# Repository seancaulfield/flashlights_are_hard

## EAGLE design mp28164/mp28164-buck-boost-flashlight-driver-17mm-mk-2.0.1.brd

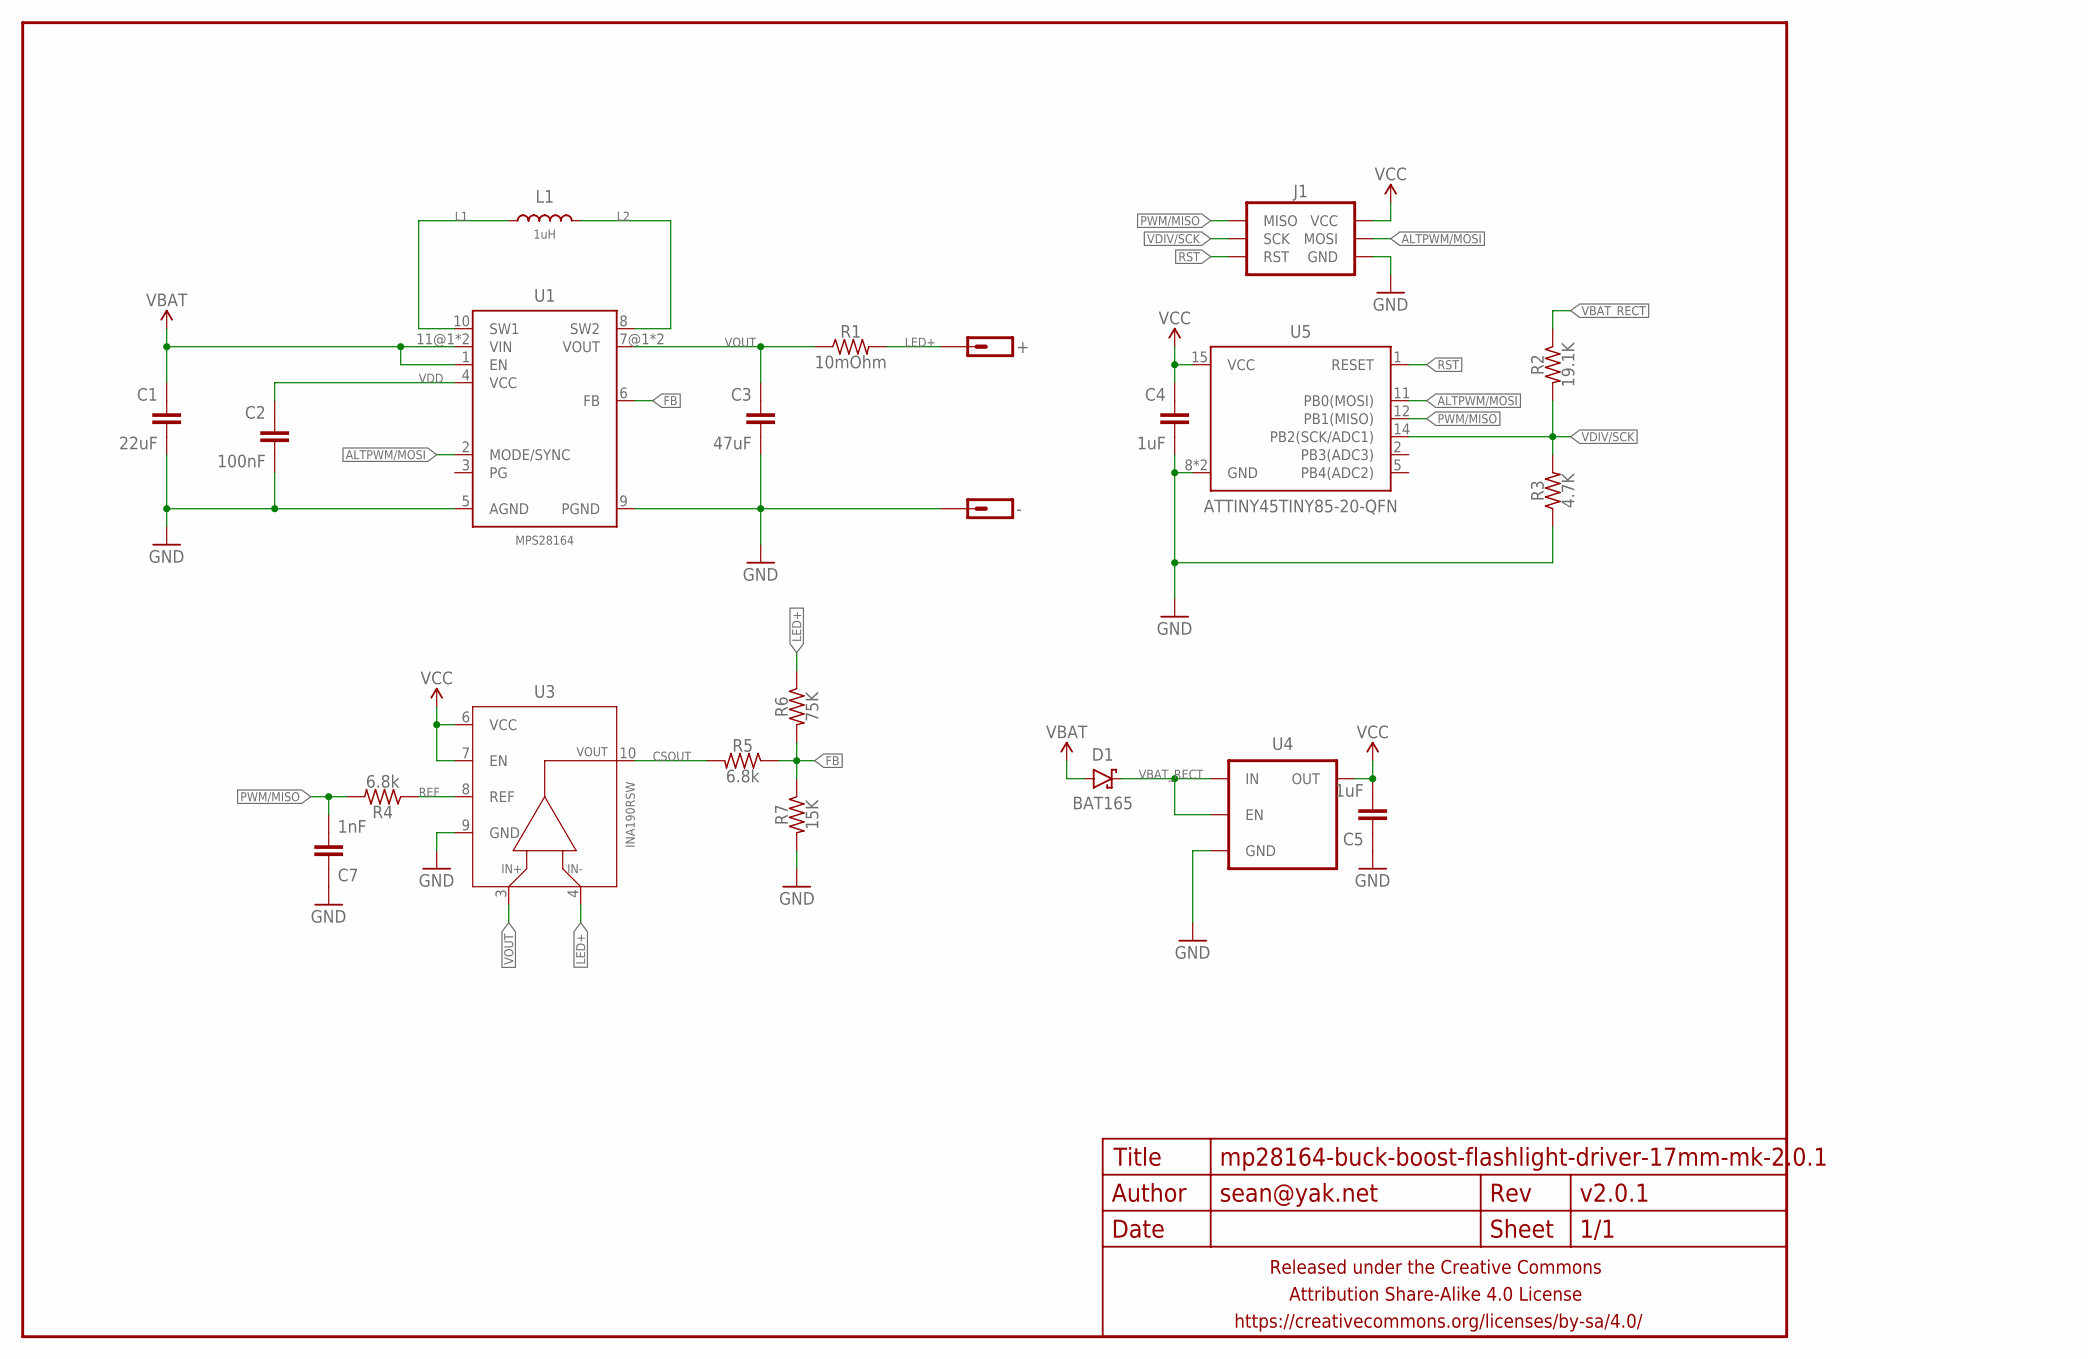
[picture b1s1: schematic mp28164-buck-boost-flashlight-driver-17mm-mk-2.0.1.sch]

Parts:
+: M01SMD-1.6MMX3.2MM-NS; 1X01-SMD-1.6MMX3.2MM-NS
-: M01SMD-1.6MMX3.2MM-NS; 1X01-SMD-1.6MMX3.2MM-NS
C1: 22uF; C1206
C2: 100nF; C0402
C3: 47uF; C1206
C4, C5: 1uF; C0402
C7: 1nF; C0402
D1: BAT165; SOD323-SCHOTTKY
FRAME1: FRAME-LETTERNO_PACKAGE; DUMMY
J1: AVR_SPI_PRG_6SMD-1.27MM; 2X3-1.27MM-SMD
L1: 1uH; XAL7070
R1: 10mOhm; R1206
R2: 19.1K; R0402
R3: 4.7K; R0402
R4, R5: 6.8k; R0402
R6: 75K; R0402
R7: 15K; R0402
U1: MPS28164
U3: INA190RSW; UQFN-10
U4: V_REG_ENTLV700; SC70
U5: ATTINY45TINY85-20-QFN; QFN20

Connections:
ALTPWM/MOSI: J1.4 (MOSI), U1.2 (MODE/SYNC), U5.11 (PB0(MOSI))
CSOUT: R5.2, U3.10 (OUT)
FB: R5.1, R6.2, R7.1, U1.6 (FB)
GND: -.P$1, C1.2, C2.2, C3.2, C4.2, C5.1, C7.1, J1.6 (GND), R3.1, R7.2, U1.5 (AGND), U1.9 (PGND), U3.9 (GND), U4.2 (GND), U5.8 (GND), U5.PAD (GND)
L1: L1.P$1 (1), U1.10 (SW1)
L2: L1.P$2 (2), U1.8 (SW2)
LED+: +.P$1, R1.2, R6.1, U3.4 (VIN-)
PWM/MISO: C7.2, J1.1 (MISO), R4.2, U5.12 (PB1(MISO))
REF: R4.1, U3.8 (REF)
RST: J1.5 (RST), U5.1 (RESET)
VBAT: C1.1, D1.A, U1.1 (EN), U1.11@1 (VIN), U1.11@2 (VIN)
VBAT_RECT: D1.C, R2.1, U4.1 (IN), U4.3 (EN)
VCC: C4.1, C5.2, J1.2 (VCC), U3.6 (VCC), U3.7 (EN), U4.5 (OUT), U5.15 (VCC)
VDD: C2.1, U1.4 (VCC)
VDIV/SCK: J1.3 (SCK), R2.2, R3.2, U5.14 (PB2(SCK/ADC1))
VOUT: C3.1, R1.1, U1.7@1 (VOUT), U1.7@2 (VOUT), U3.3 (VIN+)

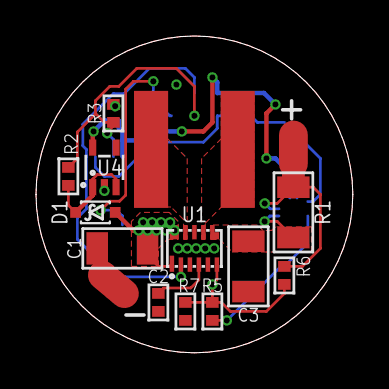
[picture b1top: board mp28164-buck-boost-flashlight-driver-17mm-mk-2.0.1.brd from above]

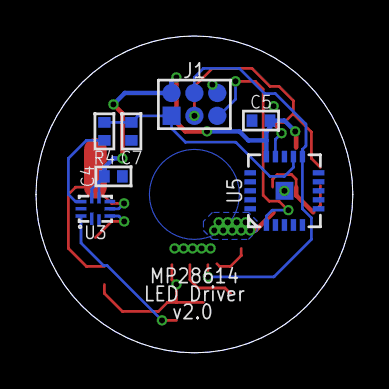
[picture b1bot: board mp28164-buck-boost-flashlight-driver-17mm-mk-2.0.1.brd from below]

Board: 2 copper layers, 17.6 x 17.6 mm, 23 parts (7 on the bottom side), 16 nets.

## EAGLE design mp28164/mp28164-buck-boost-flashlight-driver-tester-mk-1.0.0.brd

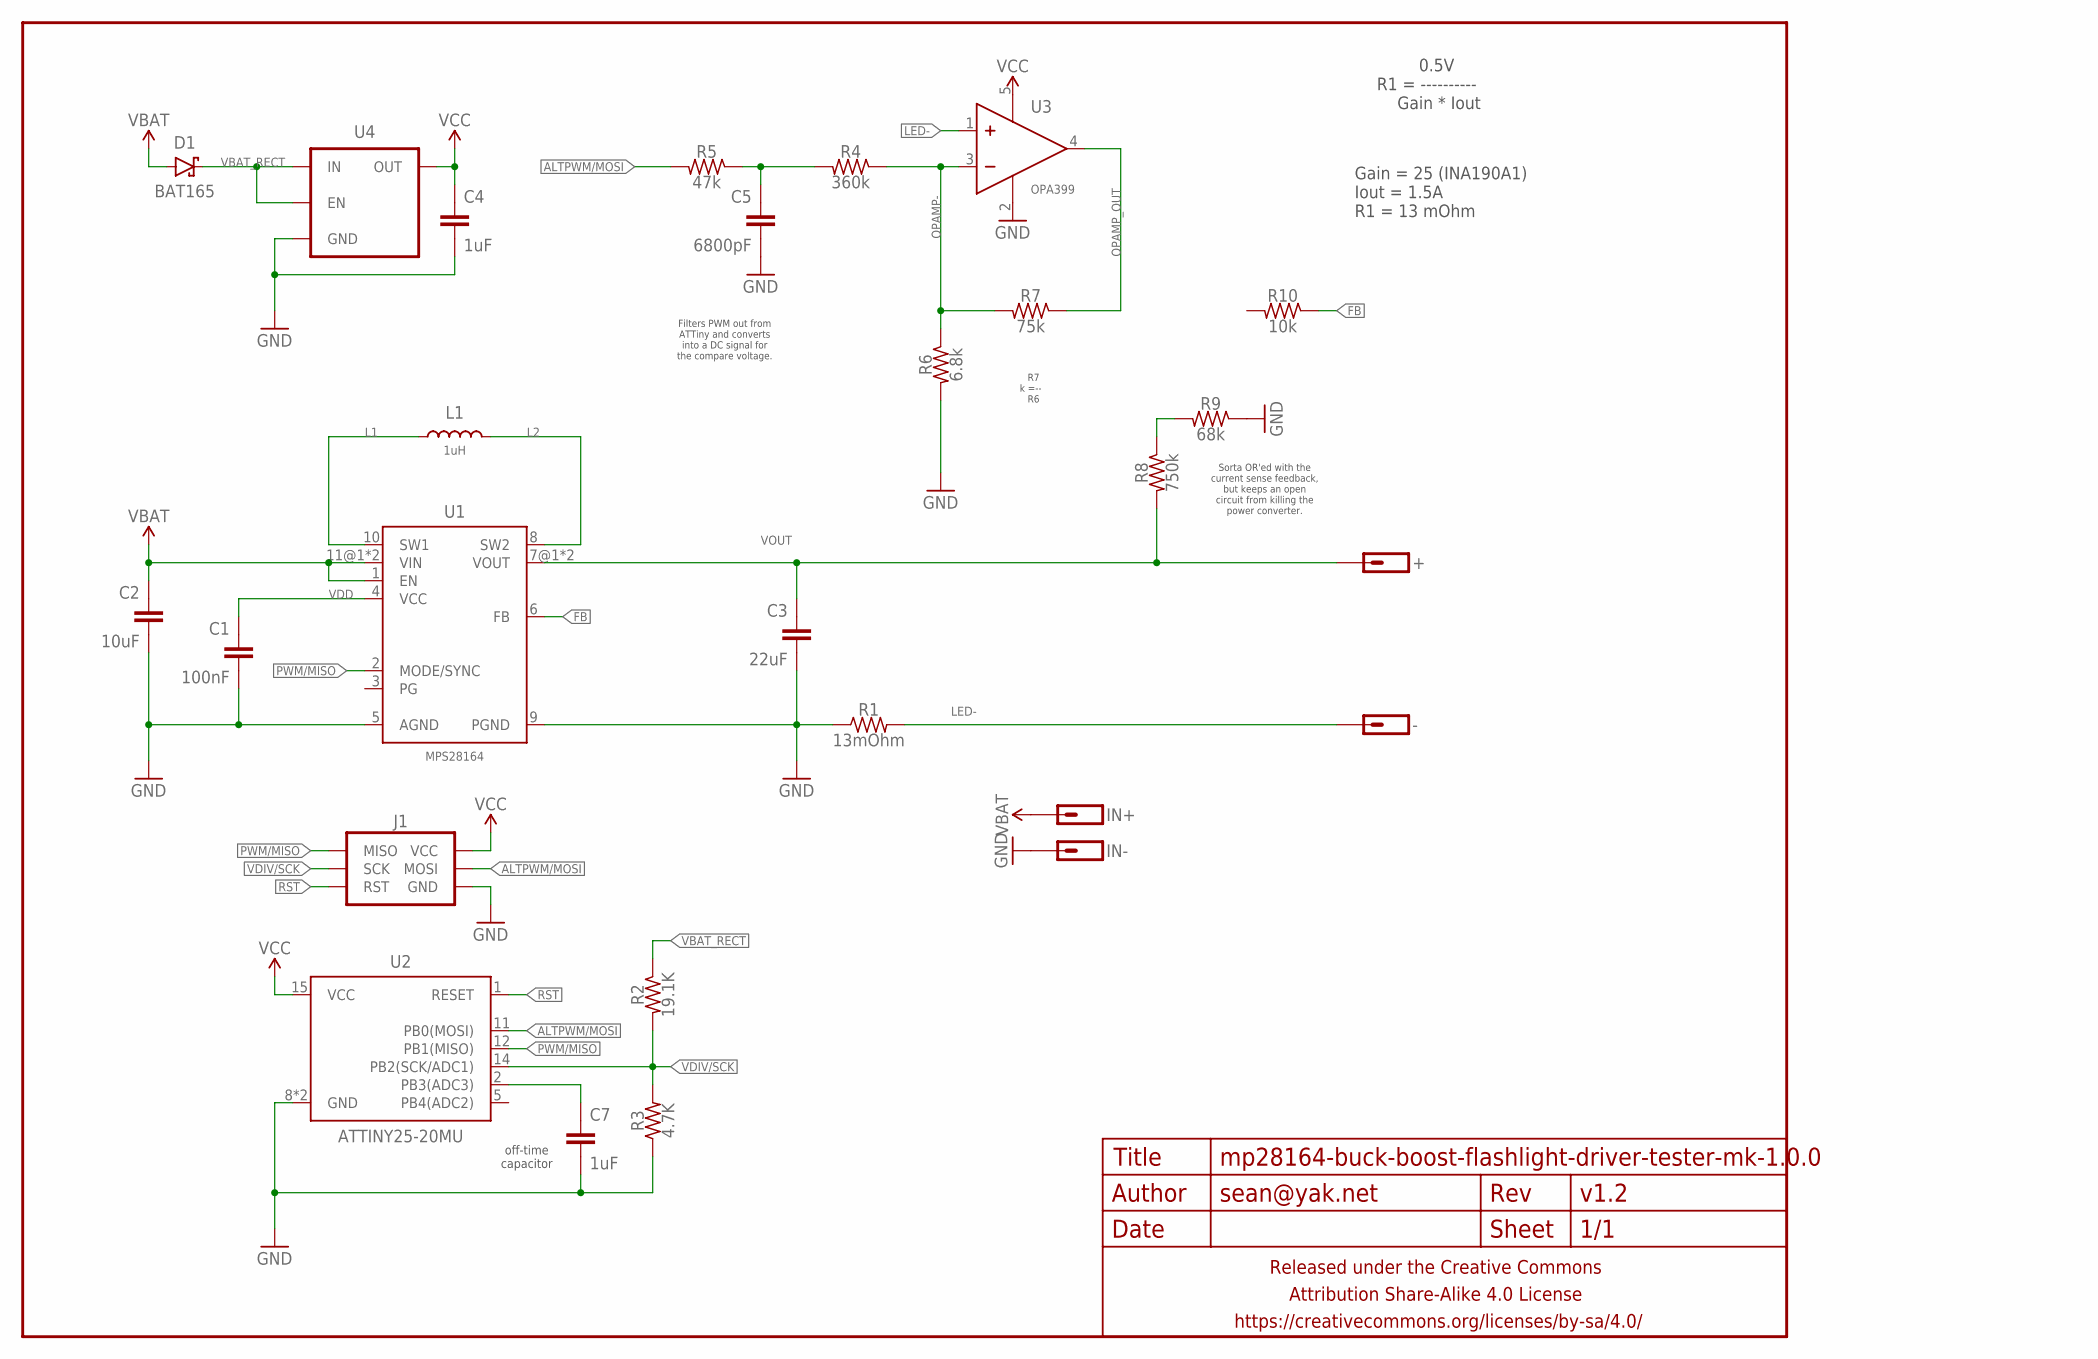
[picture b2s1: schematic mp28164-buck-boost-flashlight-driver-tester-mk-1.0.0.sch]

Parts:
+: M01PTH-1MM-CIR-NS; 1X01-1MM-CIR-NS
-: M01PTH-1MM-CIR-NS; 1X01-1MM-CIR-NS
C1: 100nF; C0402
C2: 10uF; C0805-TIGHTER
C3: 22uF; C0805-TIGHTER
C4, C7: 1uF; C0402
C5: 6800pF; C0402
D1: BAT165; SOD323-SCHOTTKY
FRAME1: FRAME-LETTERNO_PACKAGE; DUMMY
IN+: M01PTH-1MM-CIR-NS; 1X01-1MM-CIR-NS
IN-: M01PTH-1MM-CIR-NS; 1X01-1MM-CIR-NS
J1: AVR_SPI_PRG_6SMD-1.27MM; 2X3-1.27MM-SMD
L1: 1uH; XAR7030
R1: 13mOhm; R0805-TIGHTER
R2: 19.1K; R0402
R3: 4.7K; R0402
R4: 360k; R0402
R5: 47k; R0402
R6: 6.8k; R0402
R7: 75k; R0402
R8: 750k; R0402
R9: 68k; R0402
R10: 10k; R0402
U1: MPS28164
U2: ATTINY25-20MU; QFN20
U3: OPA399; SC70
U4: V_REG_ENTLV700; SC70

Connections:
ALTPWM/MOSI: J1.4 (MOSI), R5.2, U2.11 (PB0(MOSI))
FB: R10.1, U1.6 (FB)
GND: C1.2, C2.2, C3.2, C4.2, C5.2, C7.2, IN-.1, J1.6 (GND), R1.1, R3.1, R6.2, R9.1, U1.5 (AGND), U1.9 (PGND), U2.8 (GND), U2.PAD (GND), U3.2 (V-), U4.2 (GND)
L1: L1.P$1 (1), U1.10 (SW1)
L2: L1.P$2 (2), U1.8 (SW2)
LED-: -.1, R1.2, U3.1 (IN+)
unnamed: C5.1, R4.2, R5.1
unnamed: R8.1, R9.2
unnamed: C7.1, U2.2 (PB3(ADC3))
OPAMP-: R4.1, R6.1, R7.2, U3.3 (IN-)
OPAMP_OUT: R7.1, U3.4 (OUT)
PWM/MISO: J1.1 (MISO), U1.2 (MODE/SYNC), U2.12 (PB1(MISO))
RST: J1.5 (RST), U2.1 (RESET)
VBAT: C2.1, D1.A, IN+.1, U1.1 (EN), U1.11@1 (VIN), U1.11@2 (VIN)
VBAT_RECT: D1.C, R2.1, U4.1 (IN), U4.3 (EN)
VCC: C4.1, J1.2 (VCC), U2.15 (VCC), U3.5 (V+), U4.5 (OUT)
VDD: C1.1, U1.4 (VCC)
VDIV/SCK: J1.3 (SCK), R2.2, R3.2, U2.14 (PB2(SCK/ADC1))
VOUT: +.1, C3.1, R8.2, U1.7@1 (VOUT), U1.7@2 (VOUT)

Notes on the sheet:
off-time capacitor
0.5V R1 = ---------- Gain * Iout
Gain = 25 (INA190A1) Iout = 1.5A R1 = 13 mOhm
Filters PWM out from ATTiny and converts into a DC signal for the compare voltage.
R7 k =-- R6
Sorta OR'ed with the current sense feedback, but keeps an open circuit from killing the power converter.

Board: 2 copper layers, 28 parts (1 on the bottom side), 19 nets, no tracks yet.

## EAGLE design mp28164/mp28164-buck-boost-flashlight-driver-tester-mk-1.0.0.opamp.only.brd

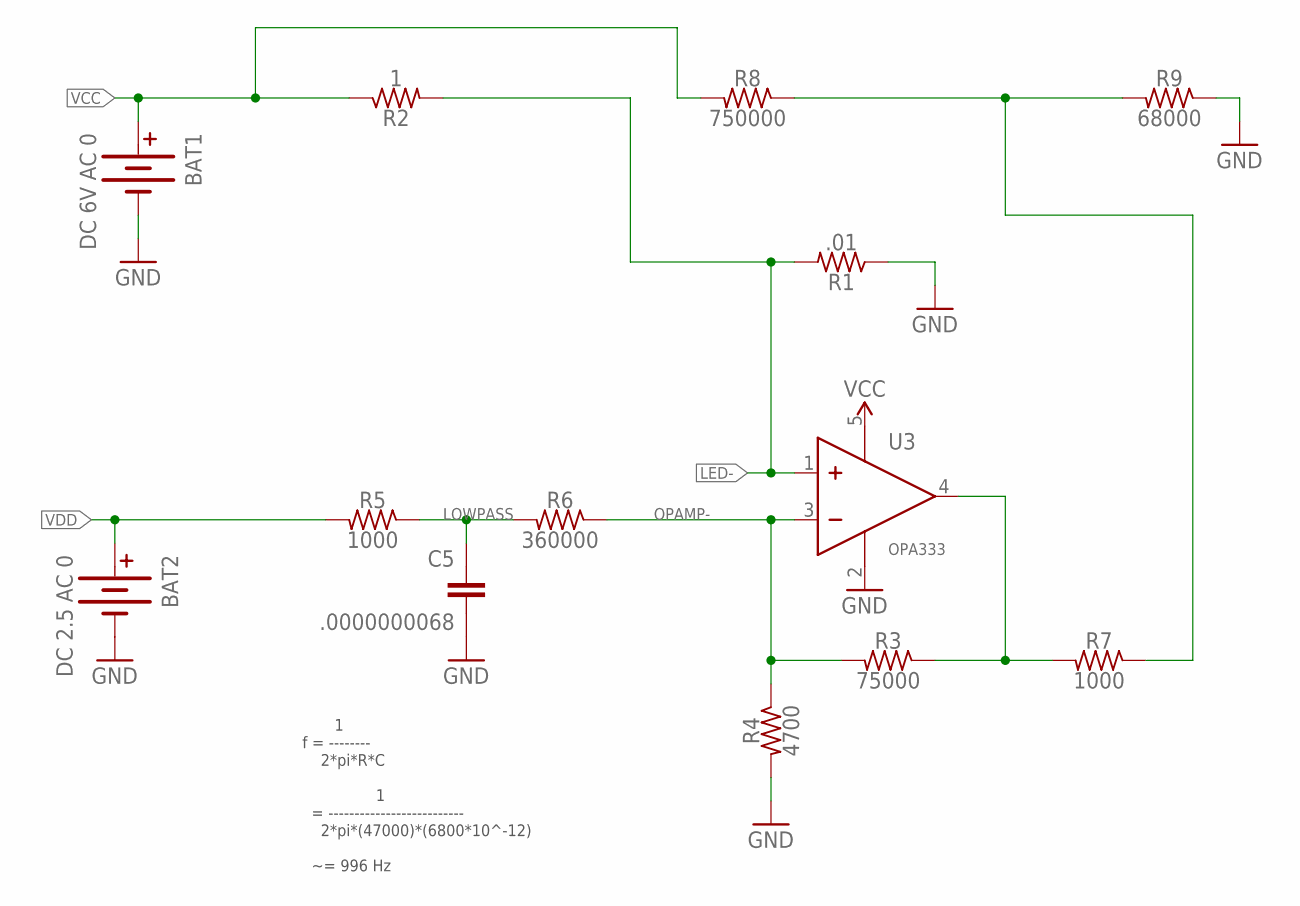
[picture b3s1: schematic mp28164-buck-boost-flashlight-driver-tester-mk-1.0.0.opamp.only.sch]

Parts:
BAT1: DC 6V AC 0; BATTCON_9V
BAT2: DC 2.5 AC 0; BATTCON_9V
C5: .0000000068; C0402
R1: .01; R0805-TIGHTER
R2: 1; R0402
R3: 75000; R0402
R4: 4700; R0402
R5, R7: 1000; R0402
R6: 360000; R0402
R8: 750000; R0402
R9: 68000; R0402
U3: OPA333; SC70

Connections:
GND: BAT1.-, BAT2.-, C5.2, R1.1, R4.2, R9.1, U3.2 (V-)
LED-: R1.2, R2.2, U3.1 (IN+)
LOWPASS: C5.1, R5.1, R6.2
unnamed: R7.1, R8.1, R9.2
OPAMP-: R3.2, R4.1, R6.1, U3.3 (IN-)
OPAMP_OUT: R3.1, R7.2, U3.4 (OUT)
VCC: BAT1.+, R2.1, R8.2, U3.5 (V+)
VDD: BAT2.+, R5.2

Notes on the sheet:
1 f = -------- 2*pi*R*C 1 = -------------------------- 2*pi*(47000)*(6800*10^-12) ~= 996 Hz

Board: 2 copper layers, 13 parts (0 on the bottom side), 8 nets, no tracks yet.

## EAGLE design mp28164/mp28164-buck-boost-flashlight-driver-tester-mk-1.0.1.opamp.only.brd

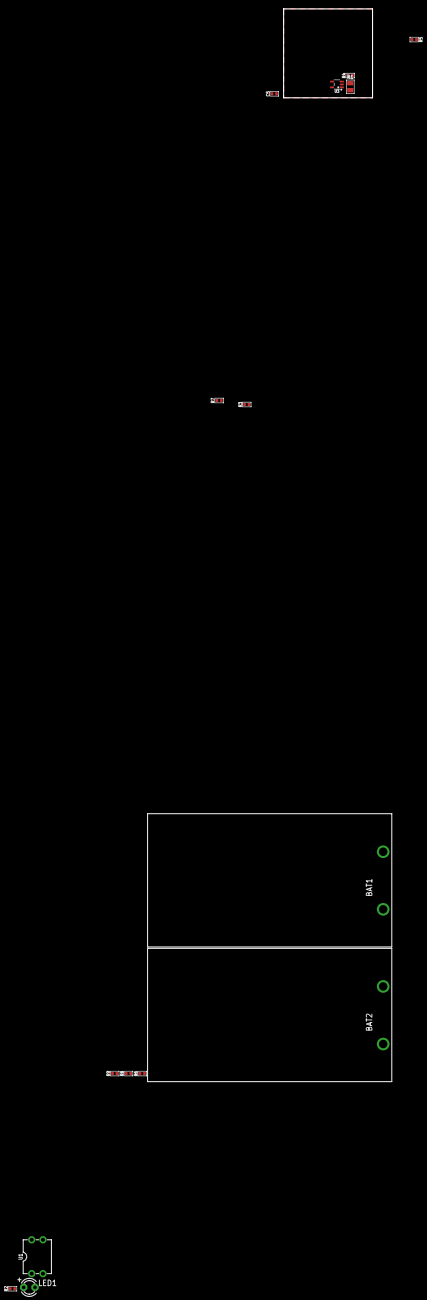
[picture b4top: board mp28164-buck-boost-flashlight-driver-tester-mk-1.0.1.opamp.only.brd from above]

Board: 2 copper layers, 20.0 x 20.0 mm, 15 parts (0 on the bottom side), 9 nets, no tracks yet.

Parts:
BAT1: DC 6.25 AC 0; BATTCON_9V
BAT2: DC 2.5 AC 0; BATTCON_9V
C5: .0000000068; C0402
LED1: LED3MM
R1: .01; R0805-TIGHTER
R2: 1000000; R0402
R3: 75000; R0402
R4, R5: 1000; R0402
R6: 100000; R0402
R7: 10000; R0402
R8: 750000; R0402
R9: 68000; R0402
U1: DIL04
U3: OPA333; SC70

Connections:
FB: R2.1, R7.1, R8.1, R9.2, U1.1
GND: BAT1.-, BAT2.-, C5.2, R1.1, R4.2, R9.1, U1.2, U3.2
LED-: LED1.K, R1.2, U3.1
LOWPASS: C5.1, R5.1, R6.2
OPAMP-: R3.2, R4.1, R6.1, U3.3
OPAMP_OUT: R3.1, R7.2, U3.4
VCC: BAT1.+, U1.3, U3.5
VDD: BAT2.+, R2.2, R5.2
VOUT: LED1.A, R8.2, U1.4

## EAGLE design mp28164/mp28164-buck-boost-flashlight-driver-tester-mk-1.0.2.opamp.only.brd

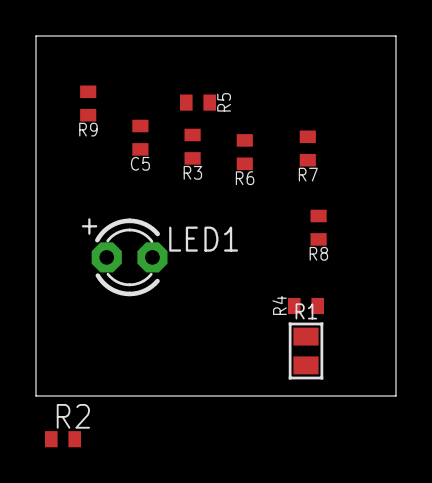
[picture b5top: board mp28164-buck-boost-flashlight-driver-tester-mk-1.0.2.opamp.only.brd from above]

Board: 2 copper layers, 20.0 x 20.0 mm, 11 parts (0 on the bottom side), 5 nets, no tracks yet.

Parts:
C5: .0000000068; C0402
LED1: LED3MM
R1: .01; R0805-TIGHTER
R2, R7: 1; R0402
R3: 15000; R0402
R4, R5: 1000; R0402
R6: 100000; R0402
R8: 750000; R0402
R9: 68000; R0402

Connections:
FB: R2.1, R8.1, R9.2
GND: C5.2, R1.1, R4.2, R6.1, R9.1
LED-: LED1.K, R1.2
LOWPASS: C5.1, R5.1, R6.2
OPAMP-: R3.2, R4.1

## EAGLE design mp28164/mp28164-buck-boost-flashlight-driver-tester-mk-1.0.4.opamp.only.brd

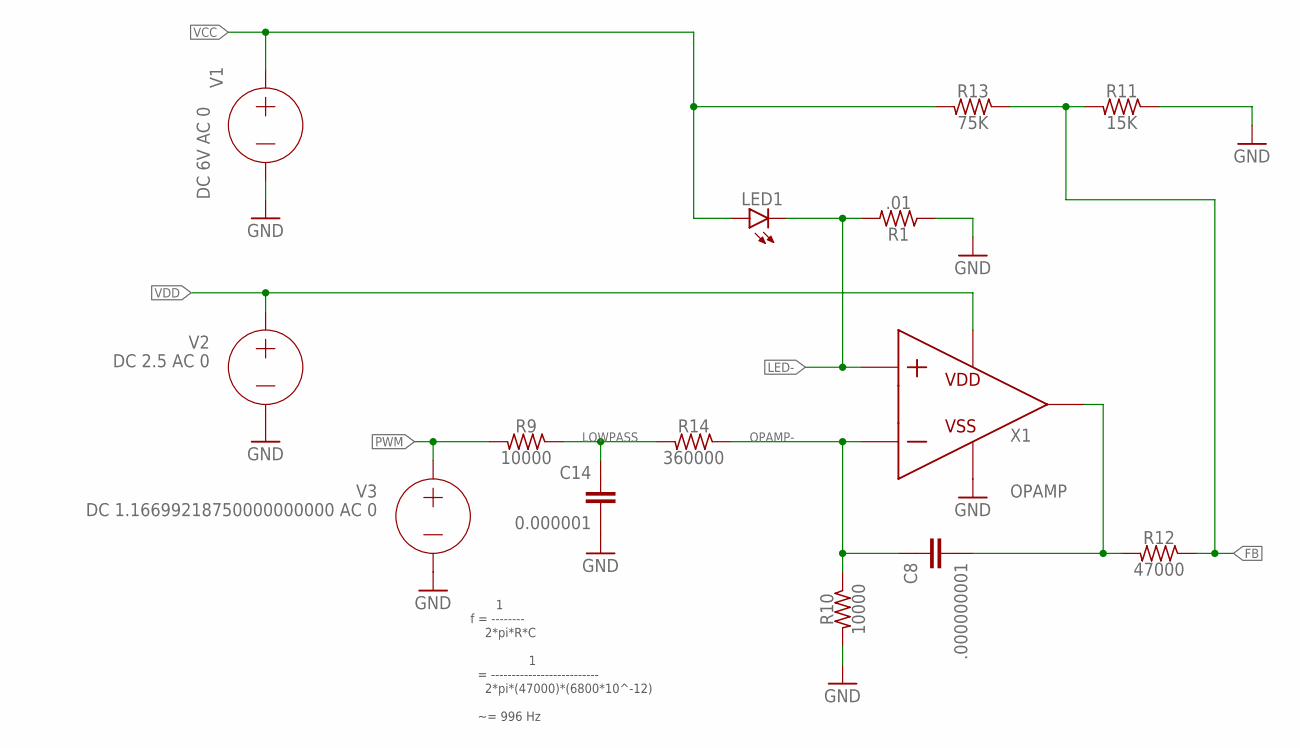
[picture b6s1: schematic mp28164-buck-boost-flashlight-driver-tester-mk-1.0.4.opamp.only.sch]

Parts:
C8: .000000001; C0402
C14: 0.000001; C0402
LED1: LED3MM
R1: .01; R0805-TIGHTER
R9, R10: 10000; R0402
R11: 15K; R0402
R12: 47000; R0402
R13: 75K; R0402
R14: 360000; R0402

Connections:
FB: R11.2, R12.1, R13.1
GND: C14.2, R1.1, R10.2, R11.1
LED-: LED1.K (C), R1.2
LOWPASS: C14.1, R9.1, R14.2
OPAMP-: C8.1, R10.1, R14.1
OPAMP_OUT: C8.2, R12.2
PWM: R9.2
VCC: LED1.A, R13.2

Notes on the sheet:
1 f = -------- 2*pi*R*C 1 = -------------------------- 2*pi*(47000)*(6800*10^-12) ~= 996 Hz

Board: 2 copper layers, 10 parts (0 on the bottom side), 7 nets, no tracks yet.

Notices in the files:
parts and their libraries:
a_parts: Released under the Creative Commons Attribution Share-Alike 4.0 License
a_parts: https://creativecommons.org/licenses/by-sa/4.0
a_parts: Released under the Creative Commons
